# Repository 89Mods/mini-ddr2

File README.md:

# mini-ddr2

DDR2 Memory Controller fit into a 1€ MAX II CPLD with just 240 LUs. Its incredibly slow, but works!

Currently only works with x4 DRAMs. To demonstrate basic functionality, the CPLD is programmed to respond to byte-wide reads/writes on a "flat" address/data bus. ``A_f`` are the 24 address lines, ``Q_f`` is the data bus. Operation is controlled via ``WEb_f`` and ``CS_f`` (not to be confused with the similarly-named DDR2 signals). A ``ready`` output indicates if the last read/write request has completed processing.

# Implementation Details

After releasing the reset input, the CPLD runs through the DDR2 initialization sequence. Slowly. I optimized it for size, not speed, so it takes several tens of thousands of clock cycles to complete. Once it does, the controller enters the main state machine.

When idle, the controller spams DDR2 refresh commands as fast as it can, only interrupted by a falling edge on ``CS_f`` requesting a memory access. ``A_f`` is split into a bank, column and row address and the proper bank and column activated before the memory access.

Both reads and writes use the minimum burst length of 4, but are only byte-wide, using the first two nibbles in the burst, least-significant half first.

At the start of any read or write leaving the idle loop, the controller starts a timer, only precharging the current bank and returning to idle mode once this expires. This allows for further reads or writes to the same bank and row to be registered and processed immediatly.

If the bank or row change, a precharge and then activate are executed to switch to the new addresses. This does not reset the timer.

# Timing

Max tested clock speed for the CPLD is 85MHz. This is divided by two to arrive at the DDR2 clock of 42.5MHz. Works fine, despite violating the min clock speed for the DDR2 chip in the example by over 150MHz.

Quartus says the design does not meet timings above this clock speed. Propagation delay times begin to mess with the timing at this stage anyways.

The best-case scenario is a sequential write, taking 12 CPLD clock cycles (141ns).

The worst case is a non-sequential read requiring a switch to a different row, at 22 CPLD clock cycles (258ns).

It may be possible to improve this by playing with the timing parameters. Sadly, this design uses 240/240 LUs, so there is otherwise no more room for improvement.

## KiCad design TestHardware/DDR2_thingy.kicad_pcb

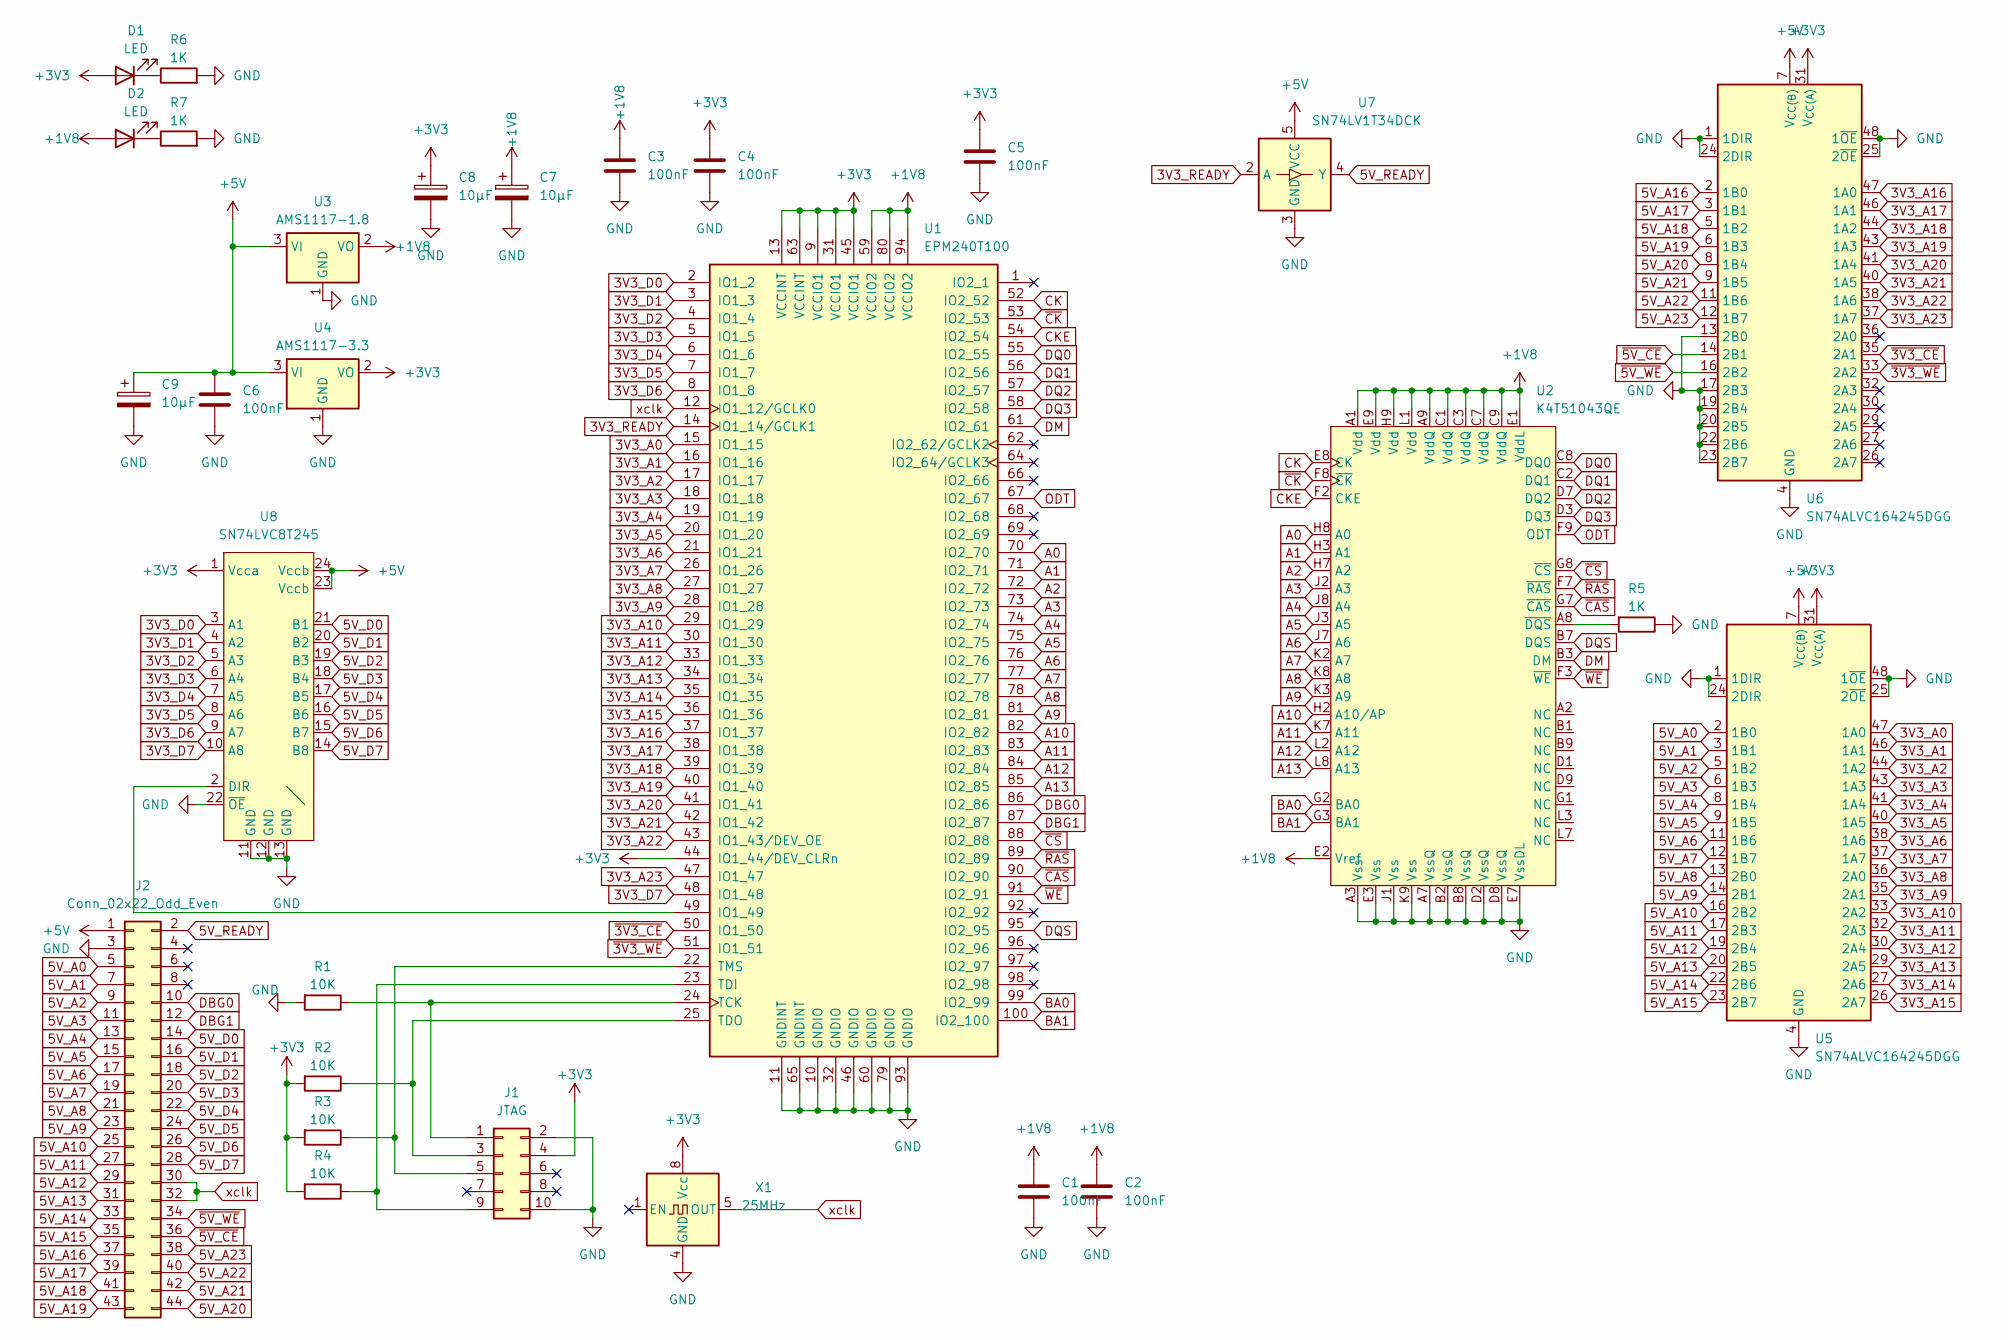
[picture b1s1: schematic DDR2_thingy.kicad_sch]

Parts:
C1, C2, C3, C4, C5, C6: 100nF; C_0805_2012Metric_Pad1.18x1.45mm_HandSolder
C7, C8, C9: 10µF; CP_Elec_3x5.4
D1, D2: LED; LED_1206_3216Metric_Pad1.42x1.75mm_HandSolder
J1: JTAG; PinHeader_2x05_P2.54mm_Vertical
J2: Conn_02x22_Odd_Even; PinHeader_2x22_P2.54mm_Vertical
R1, R2, R3, R4: 10K; R_1206_3216Metric_Pad1.30x1.75mm_HandSolder
R5: 1K; R_1206_3216Metric_Pad1.30x1.75mm_HandSolder
R6, R7: 1K; R_2010_5025Metric_Pad1.40x2.65mm_HandSolder
U1: EPM240T100; LQFP-100_14x14mm_P0.5mm
U2: K4T51043QE; BGA_for_those_ddr2_ics_1
U3: AMS1117-1.8; SOT-223-3_TabPin2
U4: AMS1117-3.3; SOT-223-3_TabPin2
U5, U6: SN74ALVC164245DGG; TSSOP-48_6.1x12.5mm_P0.5mm
U7: SN74LV1T34DCK; SOT-23-5
U8: SN74LVC8T245; TSSOP-24_4.4x7.8mm_P0.65mm
X1: 25MHz; Oscillator_DIP-8

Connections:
3V3_A0: U1.15 (IO1_15), U5.47 (1A0)
3V3_A1: U1.16 (IO1_16), U5.46 (1A1)
3V3_A2: U1.17 (IO1_17), U5.44 (1A2)
3V3_A3: U1.18 (IO1_18), U5.43 (1A3)
3V3_A4: U1.19 (IO1_19), U5.41 (1A4)
3V3_A5: U1.20 (IO1_20), U5.40 (1A5)
3V3_A6: U1.21 (IO1_21), U5.38 (1A6)
3V3_A7: U1.26 (IO1_26), U5.37 (1A7)
3V3_A8: U1.27 (IO1_27), U5.36 (2A0)
3V3_A9: U1.28 (IO1_28), U5.35 (2A1)
3V3_A10: U1.29 (IO1_29), U5.33 (2A2)
3V3_A11: U1.30 (IO1_30), U5.32 (2A3)
3V3_A12: U1.33 (IO1_33), U5.30 (2A4)
3V3_A13: U1.34 (IO1_34), U5.29 (2A5)
3V3_A14: U1.35 (IO1_35), U5.27 (2A6)
3V3_A15: U1.36 (IO1_36), U5.26 (2A7)
3V3_A16: U1.37 (IO1_37), U6.47 (1A0)
3V3_A17: U1.38 (IO1_38), U6.46 (1A1)
3V3_A18: U1.39 (IO1_39), U6.44 (1A2)
3V3_A19: U1.40 (IO1_40), U6.43 (1A3)
3V3_A20: U1.41 (IO1_41), U6.41 (1A4)
3V3_A21: U1.42 (IO1_42), U6.40 (1A5)
3V3_A22: U1.43 (IO1_43/DEV_OE), U6.38 (1A6)
3V3_A23: U1.47 (IO1_47), U6.37 (1A7)
3V3_D0: U1.2 (IO1_2), U8.3 (A1)
3V3_D1: U1.3 (IO1_3), U8.4 (A2)
3V3_D2: U1.4 (IO1_4), U8.5 (A3)
3V3_D3: U1.5 (IO1_5), U8.6 (A4)
3V3_D4: U1.6 (IO1_6), U8.7 (A5)
3V3_D5: U1.7 (IO1_7), U8.8 (A6)
3V3_D6: U1.8 (IO1_8), U8.9 (A7)
3V3_D7: U1.48 (IO1_48), U8.10 (A8)
3V3_READY: U1.14 (IO1_14/GCLK1), U7.2 (A)
5V_A0: J2.5, U5.2 (1B0)
5V_A1: J2.7, U5.3 (1B1)
5V_A2: J2.9, U5.5 (1B2)
5V_A3: J2.11, U5.6 (1B3)
5V_A4: J2.13, U5.8 (1B4)
5V_A5: J2.15, U5.9 (1B5)
5V_A6: J2.17, U5.11 (1B6)
5V_A7: J2.19, U5.12 (1B7)
5V_A8: J2.21, U5.13 (2B0)
5V_A9: J2.23, U5.14 (2B1)
5V_A10: J2.25, U5.16 (2B2)
5V_A11: J2.27, U5.17 (2B3)
5V_A12: J2.29, U5.19 (2B4)
5V_A13: J2.31, U5.20 (2B5)
5V_A14: J2.33, U5.22 (2B6)
5V_A15: J2.35, U5.23 (2B7)
5V_A16: J2.37, U6.2 (1B0)
5V_A17: J2.39, U6.3 (1B1)
5V_A18: J2.41, U6.5 (1B2)
5V_A19: J2.43, U6.6 (1B3)
5V_A20: J2.44, U6.8 (1B4)
5V_A21: J2.42, U6.9 (1B5)
5V_A22: J2.40, U6.11 (1B6)
5V_A23: J2.38, U6.12 (1B7)
5V_D0: J2.14, U8.21 (B1)
5V_D1: J2.16, U8.20 (B2)
5V_D2: J2.18, U8.19 (B3)
5V_D3: J2.20, U8.18 (B4)
5V_D4: J2.22, U8.17 (B5)
5V_D5: J2.24, U8.16 (B6)
5V_D6: J2.26, U8.15 (B7)
5V_D7: J2.28, U8.14 (B8)
5V_READY: J2.2, U7.4 (Y)
+1V8: C1.1, C2.1, C3.1, C7.1, D2.2 (A), U1.59 (VCCIO2), U1.80 (VCCIO2), U1.94 (VCCIO2), U2.A1 (Vdd), U2.A9 (VddQ), U2.C1 (VddQ), U2.C3 (VddQ), U2.C7 (VddQ), U2.C9 (VddQ), U2.E1 (VddL), U2.E2 (Vref), U2.E9 (Vdd), U2.H9 (Vdd), U2.L1 (Vdd), U3.2 (VO)
+3V3: C4.1, C5.1, C8.1, D1.2 (A), J1.4, R2.2, R3.2, R4.2, U1.9 (VCCIO1), U1.13 (VCCINT), U1.31 (VCCIO1), U1.44 (IO1_44/DEV_CLRn), U1.45 (VCCIO1), U1.63 (VCCINT), U4.2 (VO), U5.31 (V_{CC(A)}), U5.42 (V_{CC(A)}), U6.31 (V_{CC(A)}), U6.42 (V_{CC(A)}), U8.1 (Vcca), X1.8 (Vcc)
+5V: C6.1, C9.1, J2.1, U3.3 (VI), U4.3 (VI), U5.7 (V_{CC(B)}), U5.18 (V_{CC(B)}), U6.7 (V_{CC(B)}), U6.18 (V_{CC(B)}), U7.5 (VCC), U8.23 (Vccb), U8.24 (Vccb)
A0: U1.70 (IO2_70), U2.H8 (A0)
A1: U1.71 (IO2_71), U2.H3 (A1)
A2: U1.72 (IO2_72), U2.H7 (A2)
A3: U1.73 (IO2_73), U2.J2 (A3)
A4: U1.74 (IO2_74), U2.J8 (A4)
A5: U1.75 (IO2_75), U2.J3 (A5)
A6: U1.76 (IO2_76), U2.J7 (A6)
A7: U1.77 (IO2_77), U2.K2 (A7)
A8: U1.78 (IO2_78), U2.K8 (A8)
A9: U1.81 (IO2_81), U2.K3 (A9)
A10: U1.82 (IO2_82), U2.H2 (A10/AP)
A11: U1.83 (IO2_83), U2.K7 (A11)
A12: U1.84 (IO2_84), U2.L2 (A12)
A13: U1.85 (IO2_85), U2.L8 (A13)
BA0: U1.99 (IO2_99), U2.G2 (BA0)
BA1: U1.100 (IO2_100), U2.G3 (BA1)
CK: U1.52 (IO2_52), U2.E8 (CK)
CKE: U1.54 (IO2_54), U2.F2 (CKE)
DBG0: J2.10, U1.86 (IO2_86)
DBG1: J2.12, U1.87 (IO2_87)
DM: U1.61 (IO2_61), U2.B3 (DM)
DQ0: U1.55 (IO2_55), U2.C8 (DQ0)
DQ1: U1.56 (IO2_56), U2.C2 (DQ1)
DQ2: U1.57 (IO2_57), U2.D7 (DQ2)
DQ3: U1.58 (IO2_58), U2.D3 (DQ3)
DQS: U1.95 (IO2_95), U2.B7 (DQS)
GND: C1.2, C2.2, C3.2, C4.2, C5.2, C6.2, C7.2, C8.2, C9.2, J1.2, J1.10, J2.3, R1.2, R5.1, R6.2, R7.2, U1.10 (GNDIO), U1.11 (GNDINT), U1.32 (GNDIO), U1.46 (GNDIO), U1.60 (GNDIO), U1.65 (GNDINT), U1.79 (GNDIO), U1.93 (GNDIO), U2.A3 (Vss), U2.A7 (VssQ), U2.B2 (VssQ), U2.B8 (VssQ), U2.D2 (VssQ), U2.D8 (VssQ), U2.E3 (Vss), U2.E7 (VssDL), U2.J1 (Vss), U2.K9 (Vss), U3.1 (GND), U4.1 (GND), U5.1 (1DIR), U5.4 (GND), U5.10 (GND), U5.15 (GND), U5.21 (GND), U5.24 (2DIR), U5.25 (2~OE), U5.28 (GND), U5.34 (GND), U5.39 (GND), U5.45 (GND), U5.48 (1~OE), U6.1 (1DIR), U6.4 (GND), U6.10 (GND), U6.13 (2B0), U6.15 (GND), U6.17 (2B3), U6.19 (2B4), U6.20 (2B5), U6.21 (GND), U6.22 (2B6), U6.23 (2B7), U6.24 (2DIR), U6.25 (2~OE), U6.28 (GND), U6.34 (GND), U6.39 (GND), U6.45 (GND), U6.48 (1~OE), U7.3 (GND), U8.11 (GND), U8.12 (GND), U8.13 (GND), U8.22 (~OE), X1.4 (GND)
unnamed: D1.1 (K), R6.1
unnamed: D2.1 (K), R7.1
unnamed: J1.1, R1.1, U1.24 (TCK)
unnamed: J1.3, R2.1, U1.25 (TDO)
unnamed: J1.5, R3.1, U1.22 (TMS)
unnamed: J1.9, R4.1, U1.23 (TDI)
unnamed: U1.49 (IO1_49), U8.2 (DIR)
unnamed: R5.2, U2.A8 (~DQS)
ODT: U1.67 (IO2_67), U2.F9 (ODT)
xclk: J2.30, J2.32, U1.12 (IO1_12/GCLK0), X1.5 (OUT)
~3V3_CE: U1.50 (IO1_50), U6.35 (2A1)
~3V3_WE: U1.51 (IO1_51), U6.33 (2A2)
~5V_CE: J2.36, U6.14 (2B1)
~5V_WE: J2.34, U6.16 (2B2)
~CAS: U1.90 (IO2_90), U2.G7 (~CAS)
~CK: U1.53 (IO2_53), U2.F8 (~CK)
~CS: U1.88 (IO2_88), U2.G8 (~CS)
~RAS: U1.89 (IO2_89), U2.F7 (~RAS)
~WE: U1.91 (IO2_91), U2.F3 (~WE)

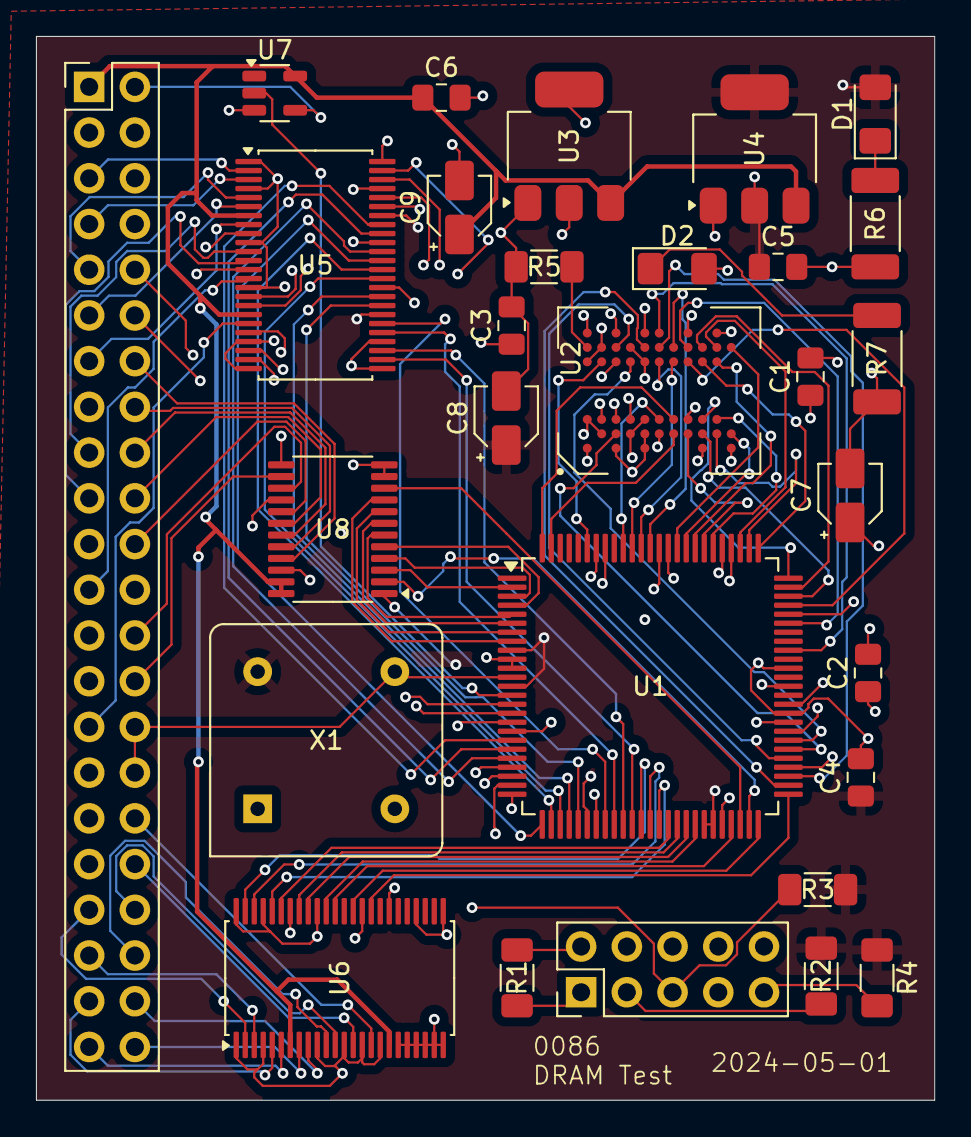
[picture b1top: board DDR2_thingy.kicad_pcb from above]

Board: 4 copper layers, 49.9 x 59.1 mm, 29 parts (0 on the bottom side), 115 nets.

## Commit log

2024-06-17 Initial commit.
2024-06-17 Major speed improvements.
